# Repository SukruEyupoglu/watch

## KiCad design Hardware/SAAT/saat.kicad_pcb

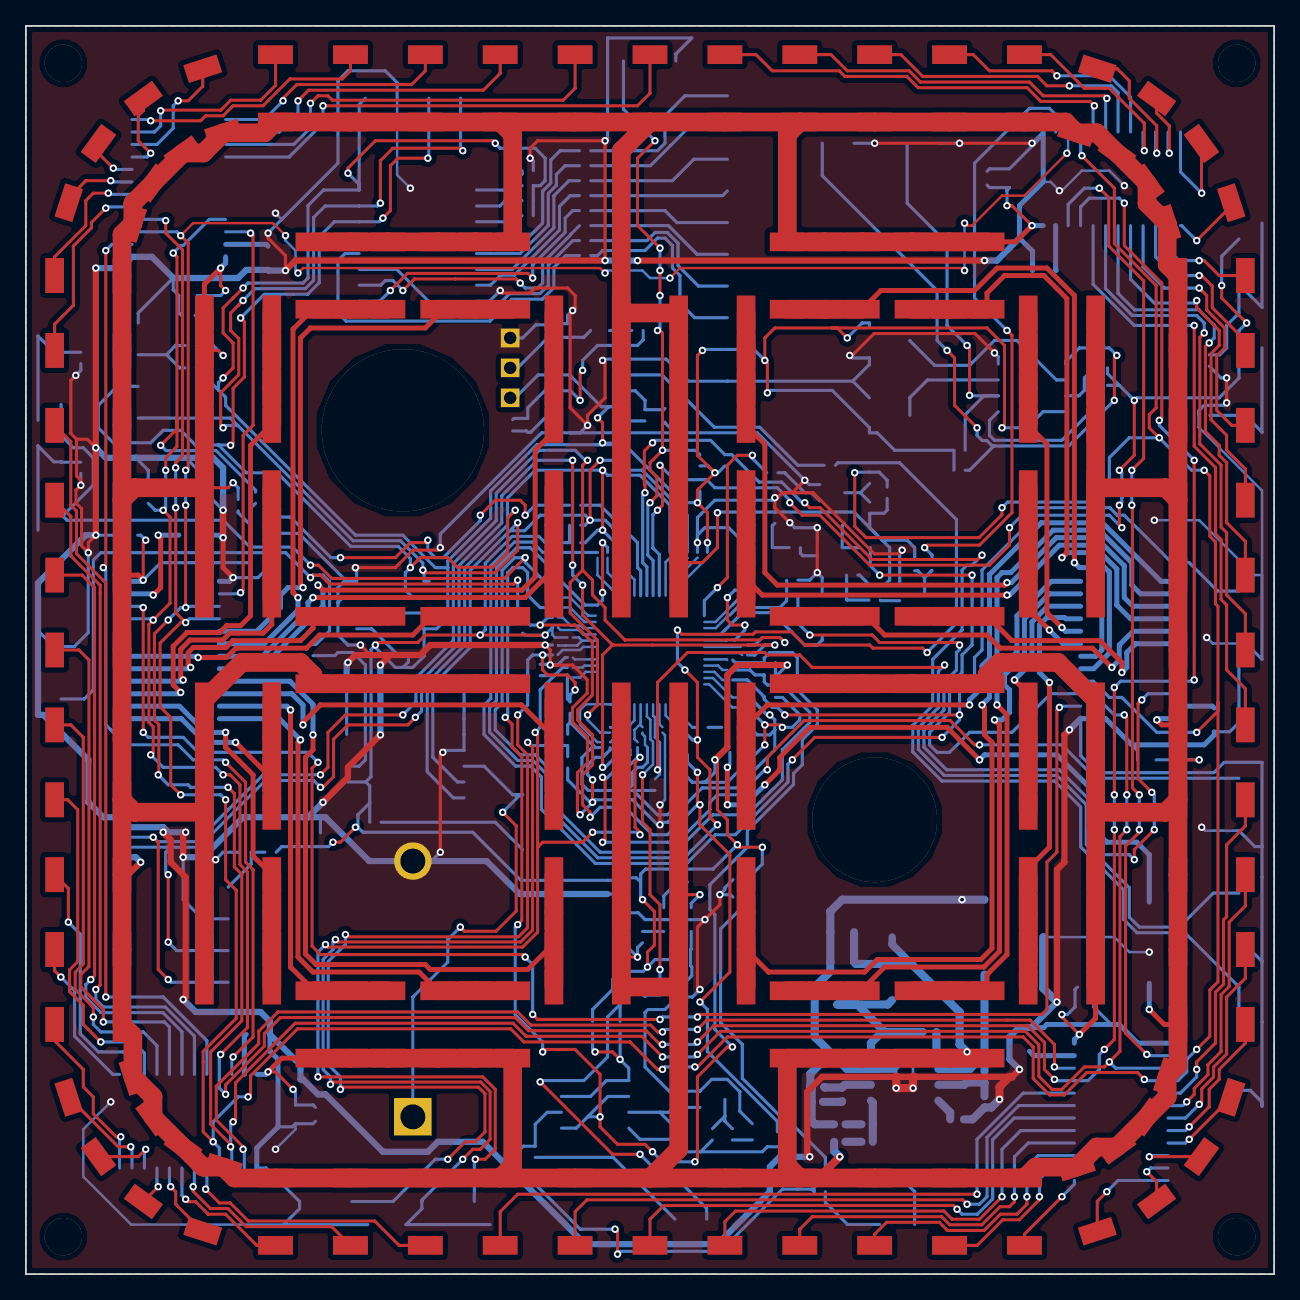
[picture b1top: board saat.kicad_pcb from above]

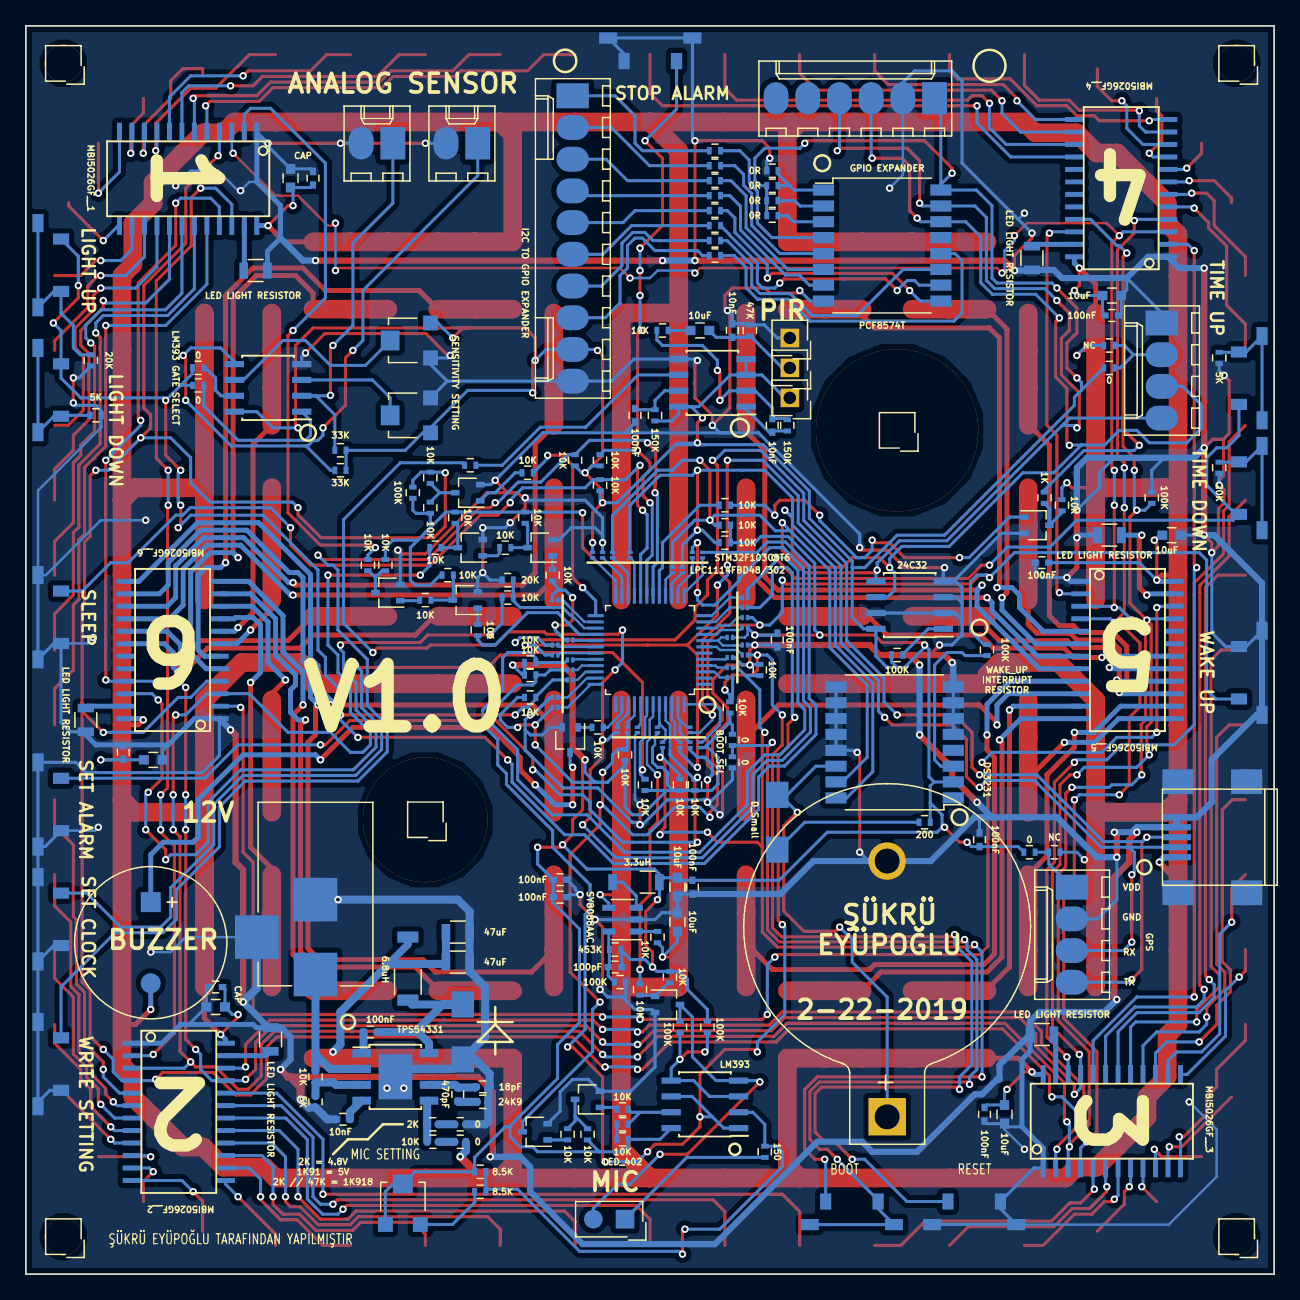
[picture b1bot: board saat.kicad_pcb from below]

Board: 2 copper layers, 100.0 x 100.0 mm, 387 parts (227 on the bottom side), 243 nets.

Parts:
BT1: Battery; Keystone_103_1x20mm-CoinCell
C1, C2, C3, C4, C8, C10, C12, C14, C16, C18, C20, C21, C31: 100nF; C_0402
C5, C7, C9, C11, C13, C15, C17, C19, C23: 10uF; C_0603
C6: 100pF; C_0402
C22, C24, C26: 10nF; C_0402
C27: 470pF; C_0402
C28: 18pF; C_0402
C29, C30: 47uF; L_0805
D1: LED_402; R_0402
D2, D300: D_Small; DO-214AC
D3, D4, D5, D6, D7, D8, D9, D10, D11, D12, D13, D14, D15, D16, D17, D18, D19, D20, D21, D22, D23, D24, D25, D26, D27, D28, D29, D30, D31, D32, D33, D34, D35, D36, D37, D38, D39, D40, D41, D42, D43, D44, D45, D46, D47, D48, D49, D50, D51, D52, D53, D54, D57, D58, D59, D61, D62, D63, D66, D67, D68, D69, D70, D71, D72, D73, D74, D75, D76, D77, D79, D80, D81, D84, D85, D86, D89, D90, D91, D92, D94, D95, D96, D98, D99, D101, D103, D104, D105, D106, D108, D109, D110, D111, D113, D114, D115, D116, D118, D119, D120, D121, D123, D125, D126, D129, D130, D131, D133, D134, D135, D136, D138, D139, D140, D141, D143, D144, D145, D146, D148, D150, D151, D153, D154, D155, D158, D159, D160, D161, D163, D164, D165, D166, D168, D169, D170, D171, D173, D174, D175, D176, D179, D180, D181, D183, D184, D185, D188, D189, D190, D191, D193, D194, D195, D196, D198, D199, D200, D201: 5730; LED_5730
J1: USB_B; USB_Mini-B
J14: Barrel_Jack; BARREL_JACK
J101, J102, J103, J104, J105, J201: Screw_Terminal_01x01; HEADER-1x01
J106, J107, J108: PIR; HEADER-1x01
J109, J200: OLED; Molex_KK-6410-04_04x2.54mm_Straight
J110: Conn_01x10; Molex_KK-6410-10_10x2.54mm_Straight
J111, J112: Conn_01x02; Molex_KK-6410-02_02x2.54mm_Straight
J113: Conn_01x06; Molex_KK-6410-06_06x2.54mm_Straight
L1: 3.3uH; L_0805
L2: 6.8uH; L_1206
NC1, NC2, NC3, NC4, NC5, NC6, NC7, NC8, NC9, NC10, NC11, NC12, NC13, NC14, NC15, NC16, NC17, NC18, NC19, NC20, NC21, NC22, NC23, NC24, NC25, NC26, NC27, NC28, NC29, NC30, NC31, NC32, NC33, NC34, NC35, NC36: 0; R_0201
Q1, Q2, Q3, Q4, Q5, Q6, Q7, Q8, Q9, Q10: Q_NPN_BEC; SOT-323-TRANSISTOR
R1, R3, R5, R36, R54, R55, R400: 100K; R_0402
R2: 150; R_0402
R4, R6, R7, R8, R9, R11, R12, R13, R14, R15, R16, R17, R20, R21, R23, R24, R25, R26, R28, R29, R30, R31, R32, R33, R34, R37, R38, R39, R40, R41, R42, R43, R44, R45, R46, R47, R48, R49, R101, R127, R130: 10K; R_0402
R10: 200; R_0402
R18, R19, R126, R129: 0; R_0402
R22, R103: 1K; R_0402
R27, R50, R52: 20K; R_0402
R35: 453K; R_0402
R51, R53, R111, R112, R113, R114, R115, R116, R117, R118, R120, R121, R124: 5K; R_0402
R56, R57, R58, R59: 500; R_0805
R60, R61: 50; R_0805
R100: 47K; R_0402
R102, R104: 150K; R_0402
R105, R106, R107, R108, R109, R110, R201, R202: 0R; R_0402
R119, R122: 33K; R_0402
R125: 24K9; R_0402
R128: 2K; R_0402
RV1, RV2, RV3: POT; Potentiometer_Trimmer-EVM3E
SP1: AL11P; BUZZER
SW1, SW2, SW3: SW_Push; TS-1236VW
SW4: STOP_ALARM; TS-1236VW
SW5: SLEEP; TS-1236VW
SW6: SET_CLOCK; TS-1236VW
SW7: SET_ALARM; TS-1236VW
SW8: WRITE_SETTING; TS-1236VW
SW9, SW11: UP; TS-1236VW
SW10, SW12: DOWN; TS-1236VW
U1: MIC_ELECTRET; HEADER-2x01
U2: 24C32; SOIC-8-EEPROM
U3: LM393; SOIC-8-LM393
U4: LPC1114FBD48/301; QFP-48-LPC1114
U5: DS3231; SOP-16-DS3231
U6: SY8088AAC; SOT-23-5-SY8088AAC
U7, U8, U9, U10, U11, U12: MBI5026GF; SOP-24_P1mm
U100: EG4001; SOIC-8-LM393
U101: PCF8574T; SOP-16-PCF8574T
U102: LM3931; SOIC-8-LM393
U103: TPS54331; SO-8_POWER_PLANE
VR1, VR2: 8.5K; R_0402

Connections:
+3V3: C1.1, C2.1, C3.1, C4.1, C6.1, C7.1, C8.1, D1.2, J106.1, J110.9, J113.1, L1.2, NC5.1, NC6.1, NC17.2, NC25.2, NC31.2, NC33.2, R1.1, R4.1, R5.1, R8.1, R10.2, R11.1, R12.1, R13.1, R14.1, R16.1, R18.1, R35.1, R40.1, R43.2, R44.2, R45.2, R46.2, R47.2, R48.2, R49.2, R104.2, R106.2, R108.2, R109.2, R110.2, R119.1, R122.2, R202.2, RV1.1, RV1.2, RV2.1, RV3.3, U2.8, U3.8, U5.2, U100.3, U100.4, U100.8, U101.16, U102.8, VR2.1
+5V: C5.1, C9.1, C10.1, C11.1, C12.1, C13.1, C14.1, C15.1, C16.1, C17.1, C18.1, C19.1, C20.1, C29.1, C30.1, D3.2, D4.2, D5.2, D6.2, D7.2, D8.2, D9.2, D10.2, D11.2, D12.2, D13.2, D14.2, D15.2, D16.2, D17.2, D18.2, D19.2, D20.2, D21.2, D22.2, D23.2, D24.2, D25.2, D26.2, D27.2, D28.2, D29.2, D30.2, D31.2, D32.2, D33.2, D34.2, D35.2, D36.2, D37.2, D38.2, D39.2, D40.2, D41.2, D42.2, D43.2, D44.2, D45.2, D46.2, D47.2, D48.2, D49.2, D50.2, D51.2, D52.2, D53.2, D54.2, D57.2, D58.2, D59.2, D61.2, D62.2, D63.2, D66.2, D67.2, D68.2, D69.2, D70.2, D71.2, D72.2, D73.2, D74.2, D75.2, D76.2, D77.2, D79.2, D80.2, D81.2, D84.2, D85.2, D86.2, D89.2, D90.2, D91.2, D92.2, D94.2, D95.2, D96.2, D98.2, D99.2, D101.2, D103.2, D104.2, D105.2, D106.2, D108.2, D109.2, D110.2, D111.2, D113.2, D114.2, D115.2, D116.2, D118.2, D119.2, D120.2, D121.2, D123.2, D125.2, D126.2, D129.2, D130.2, D131.2, D133.2, D134.2, D135.2, D136.2, D138.2, D139.2, D140.2, D141.2, D143.2, D144.2, D145.2, D146.2, D148.2, D150.2, D151.2, D153.2, D154.2, D155.2, D158.2, D159.2, D160.2, D161.2, D163.2, D164.2, D165.2, D166.2, D168.2, D169.2, D170.2, D171.2, D173.2, D174.2, D175.2, D176.2, D179.2, D180.2, D181.2, D183.2, D184.2, D185.2, D188.2, D189.2, D190.2, D191.2, D193.2, D194.2, D195.2, D196.2, D198.2, D199.2, D200.2, D201.2, J1.1, L2.2, R21.1, R24.1, R25.1, R31.1, R32.1, R38.1, R39.1, R54.1, R105.2, R126.2, R201.2, SP1.2, U6.4, U7.24, U8.24, U9.24, U10.24, U11.24, U12.24
/ADC0: NC14.1, NC29.2, R4.2, U3.1, U3.6
/BOOT: NC10.1, NC35.2, R14.2, R15.1, SW2.1
/BUZZER: R20.1, U4.38
/MIC_RESET: R37.1, U4.43
/MISO: R27.1, R29.1, U4.27
/MOSI: R30.1, U4.28
/PWM: R17.1, U4.17
/RESET: NC8.1, NC9.1, R16.2, SW3.1
/SCK: NC13.1, NC28.2, R28.1
/SSEL_NSS: R23.1, U4.25
/Sheet_1/VSE: R127.1, R128.2, U103.5
/Sheet_2/7_1_1: D148.1, D150.1, D151.1, U11.5
/Sheet_2/7_1_2: D153.1, D154.1, D155.1, U11.6
/Sheet_2/7_2_1: D158.1, D159.1, D160.1, D161.1, U11.7
/Sheet_2/7_2_2: D163.1, D164.1, D165.1, D166.1, U11.8
/Sheet_2/7_3_1: D168.1, D169.1, D170.1, D171.1, U11.9
/Sheet_2/7_3_2: D173.1, D174.1, D175.1, D176.1, U11.10
/Sheet_2/7_4_1: D179.1, D180.1, D181.1, U11.11
/Sheet_2/7_4_2: D183.1, D184.1, D185.1, U11.12
/Sheet_2/7_5_1: D188.1, D189.1, D190.1, D191.1, U11.13
/Sheet_2/7_5_2: D193.1, D194.1, D195.1, D196.1, U11.14
/Sheet_2/7_6_1: D198.1, D199.1, D200.1, D201.1, U11.15
/Sheet_2/7_6_2: D74.1, D75.1, D76.1, D77.1, U11.16
/Sheet_2/7_7_1: D79.1, D80.1, D81.1, U11.17
/Sheet_2/7_7_2: D84.1, D85.1, D86.1, U11.18
/Sheet_2/14_1_1: D94.1, D95.1, D96.1, U12.5
/Sheet_2/14_1_2: D98.1, D99.1, D101.1, U12.6
/Sheet_2/14_2_1: D103.1, D104.1, D105.1, D106.1, U12.7
/Sheet_2/14_2_2: D108.1, D109.1, D110.1, D111.1, U12.8
/Sheet_2/14_3_1: D113.1, D114.1, D115.1, D116.1, U12.9
/Sheet_2/14_3_2: D118.1, D119.1, D120.1, D121.1, U12.10
/Sheet_2/14_4_1: D123.1, D125.1, D126.1, U12.11
/Sheet_2/14_4_2: D129.1, D130.1, D131.1, U12.12
/Sheet_2/14_5_1: D133.1, D134.1, D135.1, D136.1, U12.13
/Sheet_2/14_5_2: D138.1, D139.1, D140.1, D141.1, U12.14
/Sheet_2/14_6_1: D143.1, D144.1, D145.1, D146.1, U12.15
/Sheet_2/14_6_2: D51.1, D52.1, D53.1, D54.1, U12.16
/Sheet_2/14_7_1: D57.1, D58.1, D59.1, U12.17
/Sheet_2/14_7_2: D61.1, D62.1, D63.1, U12.18
/Sheet_2/SHIFT_0: U7.22, U8.2
/Sheet_2/SHIFT_1: U8.22, U9.2
/Sheet_2/SHIFT_2: U9.22, U10.2
/Sheet_2/SHIFT_3: U10.22, U11.2
/Sheet_2/SHIFT_4: U11.22, U12.2
/WAKE_UP: NC1.1, NC21.2, Q2.3, R13.2, R400.2, SW1.1
GND: BT1.2, C1.2, C2.2, C3.2, C4.2, C5.2, C7.2, C8.2, C9.2, C10.2, C11.2, C12.2, C13.2, C14.2, C15.2, C16.2, C17.2, C18.2, C19.2, C20.2, C21.2, C24.2, C26.2, C28.2, C29.2, C30.2, D300.2, J1.4, J1.5, J1.6, J14.2, J14.3, J108.1, J109.1, J110.10, J111.2, J112.2, J113.2, J200.2, NC4.1, NC15.1, NC16.1, NC23.2, NC24.2, NC36.2, Q1.2, Q2.2, Q3.2, Q4.2, Q5.2, Q6.2, Q7.2, Q8.2, Q9.2, Q10.2, R15.2, R19.2, R27.2, R36.2, R50.1, R51.1, R52.1, R53.1, R55.1, R56.1, R57.1, R58.1, R59.1, R60.1, R61.1, R100.2, R107.2, R124.1, R125.1, R129.1, RV2.3, RV3.1, SW1.2, SW3.2, SW4.2, SW5.2, SW6.2, SW7.2, SW8.2, U2.2, U2.3, U2.4, U2.7, U5.5, U5.6, U5.7, U5.8, U5.9, U5.10, U5.11, U5.12, U5.13, U6.2, U7.1, U8.1, U9.1, U10.1, U11.1, U12.1, U100.5, U101.8, U102.4, U103.7, U103.9
GNDA: Q10.3, R3.2, U1.2, U3.4
LATCH: R26.1, R54.2, U7.4, U8.4, U9.4, U10.4, U11.4, U12.4
LIGHT_UP_DOWN: NC19.2, NC27.2, R49.1, R120.2, R121.1, SW11.1, SW12.1
unnamed: BT1.1, D2.1, U5.14
unnamed: C6.2, R35.2, R36.1, U6.5
unnamed: C21.1, R104.1, U100.7
unnamed: C22.1, R102.1, U100.1
unnamed: C22.2, R101.1, R102.2, U100.2
unnamed: C23.1, C24.1, J107.1, R100.1
unnamed: C23.2, R101.2
unnamed: C26.1, U103.4
unnamed: C27.1, C28.1, U103.6
unnamed: C27.2, R125.2
unnamed: C31.1, D300.1, L2.1, U103.8
unnamed: C31.2, U103.1
unnamed: D1.1, R6.2
unnamed: D2.2, R10.1
unnamed: D3.1, U7.5
unnamed: D4.1, U7.6
unnamed: D5.1, U7.7
unnamed: D6.1, U7.8
unnamed: D7.1, U7.9
unnamed: D8.1, U7.10
unnamed: D9.1, U7.11
unnamed: D10.1, U7.12
unnamed: D11.1, U8.5
unnamed: D12.1, U8.6
unnamed: D13.1, U8.7
unnamed: D14.1, U8.8
unnamed: D15.1, U8.9
unnamed: D16.1, U8.10
unnamed: D17.1, U8.11
unnamed: D18.1, U8.12
unnamed: D19.1, U9.5
unnamed: D20.1, U9.6
unnamed: D21.1, U9.7
unnamed: D22.1, U9.8
unnamed: D23.1, U9.9
unnamed: D24.1, U9.10
unnamed: D25.1, U9.11
unnamed: D26.1, U9.12
unnamed: D27.1, U7.20
unnamed: D28.1, U7.19
unnamed: D29.1, U7.18
unnamed: D30.1, U7.17
unnamed: D31.1, U7.16
unnamed: D32.1, U7.15
unnamed: D33.1, U7.14
unnamed: D34.1, U7.13
unnamed: D35.1, U8.20
unnamed: D36.1, U8.19
unnamed: D37.1, U8.18
unnamed: D38.1, U8.17
unnamed: D39.1, U8.16
unnamed: D40.1, U8.15
unnamed: D41.1, U8.14
unnamed: D42.1, U8.13
unnamed: D43.1, U9.20
unnamed: D44.1, U9.19
unnamed: D45.1, U9.18
unnamed: D46.1, U9.17
unnamed: D47.1, U9.16
unnamed: D48.1, U9.15
unnamed: D49.1, U9.14
unnamed: D50.1, U9.13
unnamed: D66.1, U10.5
unnamed: D67.1, U10.6
unnamed: D68.1, U10.7
unnamed: D69.1, U10.8
unnamed: D70.1, U10.9
unnamed: D71.1, U10.10
unnamed: D72.1, U10.11
unnamed: D73.1, U10.12
unnamed: D89.1, U10.16
unnamed: D90.1, U10.15
unnamed: D91.1, U10.14
unnamed: D92.1, U10.13
unnamed: J14.1, R130.2, U103.2
unnamed: J109.2, R105.1, R106.1
unnamed: J110.1, R111.1
unnamed: J110.2, R112.1
unnamed: J110.3, R113.1
unnamed: J110.4, R114.1
unnamed: J110.5, R115.1
unnamed: J110.6, R116.1
unnamed: J110.7, R117.1
unnamed: J110.8, R118.1
unnamed: J111.1, R122.1, U102.5
unnamed: J112.1, R119.2, U102.2
unnamed: J200.1, R201.1, R202.1
unnamed: L1.1, U6.3
unnamed: NC1.2, U4.10
unnamed: NC2.2, U4.14
unnamed: NC3.2, U4.22
unnamed: NC4.2, U4.23
unnamed: NC5.2, U4.36
unnamed: NC6.2, U4.48
unnamed: NC7.2, U4.21
unnamed: NC8.2, U4.7
unnamed: NC9.2, U4.3
unnamed: NC10.2, U4.4
unnamed: NC11.2, U4.15
unnamed: NC12.2, U4.16
unnamed: NC13.2, U4.29
unnamed: NC14.2, U4.32
unnamed: NC15.2, U4.5
unnamed: NC16.2, U4.41
unnamed: NC17.1, NC23.1, U4.8
unnamed: NC18.1, U4.33
unnamed: NC19.1, U4.34
unnamed: NC20.1, U4.39
unnamed: NC21.1, U4.40
unnamed: NC22.1, U4.46
unnamed: NC24.1, U4.35
unnamed: NC25.1, U4.9
unnamed: NC26.1, U4.30
unnamed: NC27.1, U4.13
unnamed: NC28.1, U4.26
unnamed: NC29.1, U4.11
unnamed: NC30.1, U4.12
unnamed: NC31.1, U4.24
unnamed: NC32.1, U4.31
unnamed: NC33.1, NC35.1, U4.44
unnamed: NC34.1, NC36.1, U4.47
unnamed: Q1.1, R7.2
unnamed: Q1.3, R8.2, R9.1
unnamed: Q2.1, R9.2
unnamed: Q3.1, R17.2
unnamed: Q3.3, R21.2, R22.1
unnamed: Q4.1, R20.2
unnamed: Q4.3, SP1.1
unnamed: Q5.1, R23.2
unnamed: Q5.3, R24.2, R26.2
unnamed: Q6.1, R28.2
unnamed: Q6.3, R31.2, R33.1
unnamed: Q7.1, R30.2
unnamed: Q7.3, R32.2, R34.1
unnamed: Q8.1, R33.2
unnamed: Q8.3, R38.2, R41.2
unnamed: Q9.1, R34.2
unnamed: Q9.3, R39.2, R42.2
unnamed: Q10.1, R37.2, R40.2
unnamed: R1.2, U2.1
unnamed: R2.1, U1.1
unnamed: R2.2, U3.2, VR1.1, VR2.2
unnamed: R3.1, R5.2, U3.3, U3.5
unnamed: R6.1, R7.1, U3.7
unnamed: R18.2, R19.1, SW2.2
unnamed: R25.2, U6.1
unnamed: R50.2, SW9.2
unnamed: R51.2, SW10.2
unnamed: R52.2, SW11.2
unnamed: R53.2, SW12.2
unnamed: R56.2, U7.23
unnamed: R57.2, U8.23
unnamed: R58.2, U9.23
unnamed: R59.2, U10.23
unnamed: R60.2, U11.23
unnamed: R61.2, U12.23
unnamed: R103.2, U100.6
unnamed: R107.1, R108.1, U101.1
unnamed: R109.1, U101.2
unnamed: R110.1, U101.3
unnamed: R111.2, U101.4
unnamed: R112.2, U101.5
unnamed: R113.2, U101.6
unnamed: R114.2, U101.7
unnamed: R115.2, U101.9
unnamed: R116.2, U101.10
unnamed: R117.2, U101.11
unnamed: R118.2, U101.12
unnamed: R120.1, U102.1
unnamed: R121.2, U102.7
unnamed: R124.2, R130.1, U103.3
unnamed: R126.1, R127.2
unnamed: R128.1, R129.2
unnamed: R400.1, U5.3
unnamed: RV1.3, VR1.2
unnamed: RV2.2, U102.3
unnamed: RV3.2, U102.6
OUT_ENABLE: R22.2, R55.2, U7.21, U8.21, U9.21, U10.21, U11.21, U12.21
PIR: NC2.1, NC20.2, R103.1
RXD_G: J1.2, J200.3, NC22.2, NC32.2
SCL: J109.3, J113.3, NC7.1, NC11.1, R12.2, U2.6, U5.16, U101.14
SDA: J109.4, J113.4, NC3.1, NC12.1, R11.2, U2.5, U5.15, U101.15
SET_ALARM: R46.1, SW7.1, U4.45
SET_CLOCK: R45.1, SW6.1, U4.42
SLEEP: R44.1, SW5.1, U4.20
SPI_CLK: R41.1, U7.3, U8.3, U9.3, U10.3, U11.3, U12.3
SPI_MISO: R29.2, U12.22
SPI_MOSI: R42.1, U7.2
STOP_ALARM: R43.1, SW4.1, U4.19
TIME_UP_DOWN: NC18.2, NC30.2, R48.1, SW9.1, SW10.1
TXD_G: J1.3, J200.4, NC26.2, NC34.2
WRITE_SETTING: R47.1, SW8.1, U4.18

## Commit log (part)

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2020-06-05 Rename stm8.c to .stm8.c
2020-06-06 Update Makefile
2020-06-08 Rename nrf_gpio.c to .nrf_gpio.c
2020-06-08 Rename nrf_gpio.h to .nrf_gpio.h
2020-06-08 Rename nrf_stm8.c to .nrf_stm8.c
2020-06-08 Rename nrf24l01.c to .nrf24l01.c
2020-06-08 Rename nrf24l01.h to .nrf24l01.h
2021-01-21 Create Makefile_v1
2022-01-18 Update i2c.c
    I2C 100khz added
2022-08-05 Rename Software/stm8/Char_LCD/stm8s.h to Software/stm8/char_lcd/stm8s.h
2022-08-05 Rename Software/stm8/Char_LCD/hc595/spi/spi.c to Software/stm8/char_lcd/hc595/spi/spi.c
2022-08-05 Rename Software/stm8/Char_LCD/hc595/spi/spi.h to Software/stm8/char_lcd/hc595/spi/spi.h
2022-08-05 Rename Software/stm8/Char_LCD/hc595/hc595.c to Software/stm8/char_lcd/hc595/hc595.c
2022-08-05 Rename Software/stm8/Char_LCD/hc595/hc595.h to Software/stm8/char_lcd/hc595/hc595.h
2022-08-05 Rename Software/stm8/Char_LCD/char_lcd.c to Software/stm8/char_lcd/char_lcd.c
2022-08-05 Rename Software/stm8/Char_LCD/char_lcd.h to Software/stm8/char_lcd/char_lcd.h
2022-08-22 Rename Software/stm8/char_lcd/char_lcd.h to Software/stm8/char_lcd/char_lcd/char_lcd.h
2022-08-22 Rename Software/stm8/char_lcd/char_lcd.c to Software/stm8/char_lcd/char_lcd/char_lcd.c
2022-08-22 Rename Software/stm8/char_lcd/delay/delay.c to Software/stm8/char_lcd/char_lcd/delay/delay.c
2022-08-22 Rename Software/stm8/char_lcd/delay/delay.h to Software/stm8/char_lcd/char_lcd/delay/delay.h
2022-08-22 Rename Software/stm8/char_lcd/hc595/hc595.h to Software/stm8/char_lcd/char_lcd/hc595/hc595.h
2022-11-28 Rename Software/stm8/ds3231/i2c/i2c.c to Software/stm8/ds3231/ds3231/i2c/i2c.c
2022-11-28 Rename Software/stm8/ds3231/i2c/i2c.h to Software/stm8/ds3231/ds3231/i2c/i2c.h
2022-11-28 Rename Software/stm8/ds3231/ds3231.c to Software/stm8/ds3231/ds3231/ds3231.c
2022-11-28 Rename Software/stm8/ds3231/ds3231.h to Software/stm8/ds3231/ds3231/ds3231.h
2022-11-28 Create Makefile
2022-11-28 Rename stm8.c to stm8.cpp
2022-11-28 Rename ds3231.c to ds3231.cpp
2023-02-22 Create LICENCE
